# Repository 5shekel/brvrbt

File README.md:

# brvrbt
synthetic emotion engines

working sketch of a working model  
muscle  /  sense  /  brain  
motor/photoresistor/transistor

excerpt from ***Vehicles Experiments in Synthetic Psychology***  

http://brvrbt.tumblr.com

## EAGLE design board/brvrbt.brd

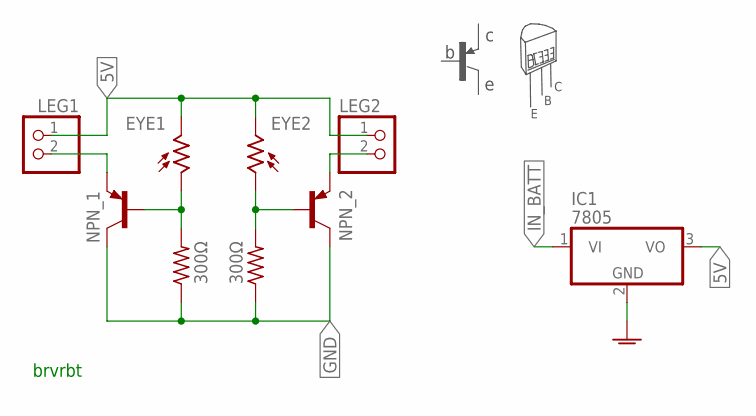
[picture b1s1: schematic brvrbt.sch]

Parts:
EYE1, EYE2: A1050_09; T0-46-A10XX
IC1: 7805; TO220V
LEG1, LEG2: HEADER-1X2; 1X02_OVAL
NPN_1: BC327-16-PNP-TO92-EBC; TO92-EBC
NPN_2: E B C; TO92-EBC
R1, R2: 300Ω; 0207/7

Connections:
5V: EYE1.2, EYE2.2, IC1.3 (VO), LEG1.1, LEG2.1
BASE_1: EYE2.1, NPN_2.B, R2.2
BASE_2: EYE1.1, NPN_1.B, R1.2
COLLECTOR_1: LEG2.2, NPN_2.E
COLLECTOR_2: LEG1.2, NPN_1.E
GND: IC1.2 (GND), NPN_1.C, NPN_2.C, R1.1, R2.1
IN_BATT: IC1.1 (VI)

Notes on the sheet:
brvrbt

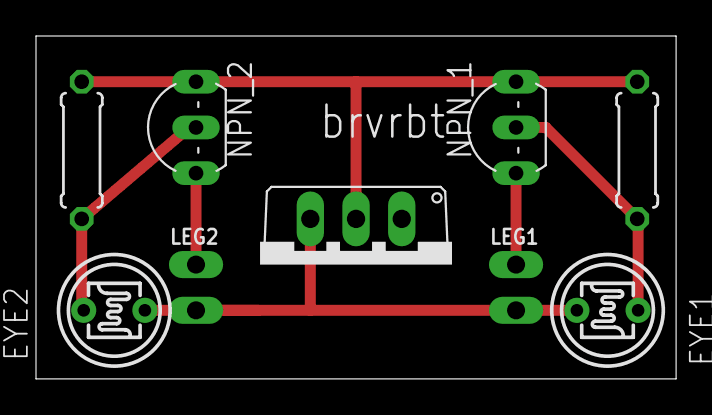
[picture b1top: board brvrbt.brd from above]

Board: 2 copper layers, 35.6 x 19.1 mm, 9 parts (0 on the bottom side), 6 nets.

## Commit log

2017-06-30 first go
2017-07-02 layout
2017-07-02 small footprint 23x19mm
2017-07-03 silk work

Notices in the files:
parts and their libraries:
microbuilder: This work is placed in the public domain, and may be freely used for commercial and non-commercial work with the following conditions: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
